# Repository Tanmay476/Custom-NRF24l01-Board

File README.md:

# Custom-NRF24l01-Board
## Overview
This repository contains files and documentation for a custom NRF24L01 board.  The board uses an NRF24L01 chip for low power wireless applications.

## Features
Custom PCB Design: Tailored board layout for optimized performance with the NRF24L01 module.
Compact and Efficient: Designed to minimize space and power usage.
Compatibility: Works with common microcontrollers such as Arduino, STM32, and ESP32.

## Power Filters
**Capacitors (C7, C8, C9):** These capacitors (33nF, 10nF, and 1nF) are used for power supply decoupling. They filter out noise and stabilize the power line to the nRF24L01+.
- Different capacitors can filter different noises, and the use of (33nF, 10nF, and 1nF) capacitors can cover a wide range of noises
- Formula: E = (1/2)CV^2
    - E: energy stored in a capacitor
    - C is the capacitance in farads (F)
    - V is the voltage across the capacitor.
**Resistor (R2):** A 22kΩ resistor used as a pull-up for the VDD line, providing stability to the power supply input.
### Crystal Oscillator Circuit (X1, C1, C2, R1)
**Crystal (X1):** A 16 MHz crystal provides a stable clock frequency for the nRF24L01+.

**Capacitors (C1, C2):** These 22pF capacitors are connected to ground and they establishes a balanced resonant condition, allowing the crystal to oscillate accurately at 16 MHz.

**Resistor (R1):** A 1MΩ resistor across the crystal to ensure proper startup of the oscillator circuit.
### RF Network (L1, L2, L3, C3, C4, C5, C6)
**Inductors (L1, L2, L3):** These inductors (8.2nH, 2.7nH, 3.9nH) are part of a matching network, helping to match the impedance of the nRF24L01+ output to the antenna.
**Capacitors (C3, C4, C5, C6):**
- C3 and C4 (2.2nF and 4.7pF): Used to filter and stabilize the RF signal.
- C5 (1.5pF) and C6 (1.0pF): Part of the antenna matching circuit to optimize RF performance.
- 50Ω Antenna Port: The network ends with a 50Ω impedance port, which is typical for RF antenna matching to ensure efficient signal transmission and reception
The main function of the nRF24L01+ chip is **wireless communication**
- **VDD:** power
- **VSS:** gound
- **DVDD:** internal digital supply output for de-coupling purpose
- **VDD_PA:** Power supply for the internal power amplifier. (must connect to ANT1 and ANT2)
- **ANT1 and ANT2:** Connections to the antenna network, allowing for the transmission and reception of RF signals.
- **XC1 and VC2:** Crystal pin
- **IREF:** reference current
- **CE (chip enable):** Controls data transmission or reception. High to enable the transceiver, and low to put it on standby.
- **CSN (SPI Chip Select):** Used to select the nRF24L01+ for SPI communication. Set low to enable SPI communication.
    - SPI communication: communication protocol used to transfer data between a master device and slave devices 
- **SCK (Serial Clock), MOSI, MISO:** These are SPI pins used for communication with a microcontroller or host device.
- **IRQ:** Interrupt request pin to signal the host of certain events, like data received or transmitted.

## Datasheet and Resources
https://www.sparkfun.com/datasheets/Components/SMD/nRF24L01Pluss_Preliminary_Product_Specification_v1_0.pdf
https://en.wikipedia.org/wiki/Impedance_matching

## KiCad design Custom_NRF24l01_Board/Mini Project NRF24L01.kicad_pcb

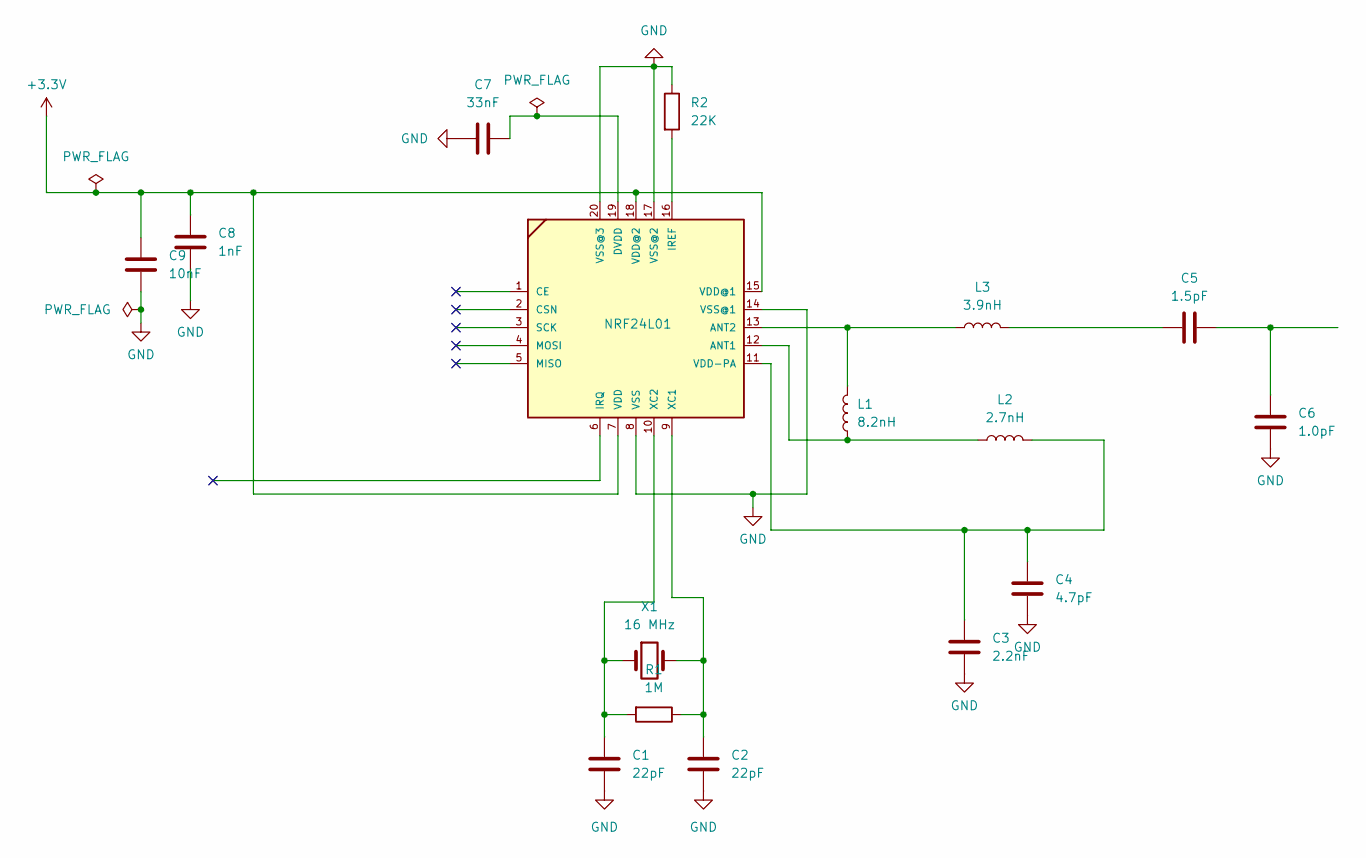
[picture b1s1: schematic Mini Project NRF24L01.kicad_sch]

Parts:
C1, C2: 22pF; C_0402_1005Metric
C3: 2.2nF; C_0402_1005Metric
C4: 4.7pF; C_0402_1005Metric
C5: 1.5pF; C_0402_1005Metric
C6: 1.0pF; C_0402_1005Metric
C7: 33nF; C_0402_1005Metric
C8: 1nF; C_0402_1005Metric
C9: 10nF; C_0402_1005Metric
L1: 8.2nH; L_0402_1005Metric
L2: 2.7nH; L_0402_1005Metric
L3: 3.9nH; L_0402_1005Metric
NRF24L01: nrf24l01 chip
R1: 1M; R_0402_1005Metric
R2: 22K; R_0402_1005Metric
X1: 16 MHz; 16 mhz 50 ppm crystal

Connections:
+3.3V: C8.1, C9.1, NRF24L01.7 (VDD), NRF24L01.15 (VDD@1), NRF24L01.18 (VDD@2)
GND: C1.2, C2.2, C3.2, C4.2, C6.2, C7.1, C8.2, C9.2, NRF24L01.8 (VSS), NRF24L01.14 (VSS@1), NRF24L01.17 (VSS@2), NRF24L01.20 (VSS@3), R2.1
unnamed: C5.1, L3.2
unnamed: C5.2, C6.1
unnamed: L1.1, L2.1, NRF24L01.12 (ANT1)
unnamed: L1.2, L3.1, NRF24L01.13 (ANT2)
unnamed: C7.2, NRF24L01.19 (DVDD)
unnamed: NRF24L01.16 (IREF), R2.2
unnamed: C3.1, C4.1, L2.2, NRF24L01.11 (VDD-PA)
unnamed: C2.1, NRF24L01.9 (XC1), R1.1, X1.2
unnamed: C1.1, NRF24L01.10 (XC2), R1.2, X1.1

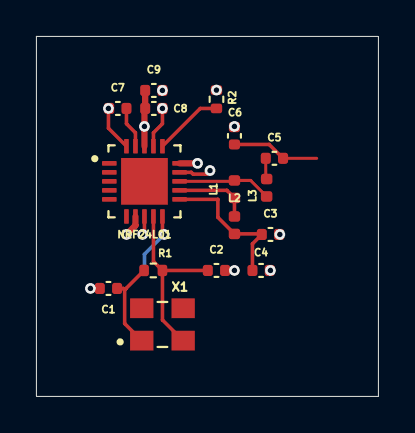
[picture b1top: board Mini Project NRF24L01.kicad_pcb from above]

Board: 4 copper layers, 19.0 x 20.0 mm, 16 parts (0 on the bottom side), 11 nets.

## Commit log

2025-01-07 Add .gitignore file
2025-01-07 Added initial Kicad files
